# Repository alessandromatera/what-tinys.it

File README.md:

# "What Tinys.it?"
### A 3D printed LED watch with Atmega328P microcontroller programmed with Arduino

#### The Story
I wanted to build a LED watch with Arduino but, searching on the web, i could not find what i was looking for. So I've decided to build my own.
I wanted to use Attiny85 microcontroller from my board [Tinys](http://www.tinys.it/) but it has only few I/O and can't be used to drive many LEDs. So i decided to use an Atmega328P (the same micro of Arduino UNO board) in TQFP package with 32 pin.

For perfect timing i've used a 32.768 KHz Crystal connected to Xtal pins of Atmega328p running in asynchronous mode. In this way i can use internal 8Mhz oscillator as main clock of the microcontroller and the overflow of timer2 (used for the external crystal) as interrupt for increase the seconds.

Why 32.768Khz Crystal? Because using prescaler to 128 we have 256 Hz, so 1 overflow/sec. It's the most used crystal for watches for this reason.

What about the name? Well, my web site is [Tinys.it](http://www.tinys.it/) :D

#### The Project
I wanted to build a watch with 60 LEDs but to keep the clock size small, i've decide to use only 32 LED (1 LED/100 seconds). But even if the microcontroller has 32 pin, they aren't all I/O: only 25 pins can be used for the 32 LEDs and the button. To drive a larger number of LEDs with few pins i've used the [Charlieplexing Matrix](http://en.wikipedia.org/wiki/Charlieplexing), in this way i can drive 6 LEDs with only 3 Pins. Becouse i can't use two different color of LEDs, to distinguish between hours and minutes, the minutes LED is blinking. 

To reduce battery drain the watch is always in sleep. To show-up the time is needed to press the button.

As the clock hands, the hours LED isn't stay in the same position: is moving a bit, consequently to minutes.

The watch is powered by a 3 Volt CR2032 battery. With this battery the LEDs resistors can be shorted.

#### The Firmware
After setup the timer2 overflow interrupt and the button change-pin interrupt, the microcontroller goes to sleep. Every time the timer2 goes overflow (1 overflow/seconds) the microcontroller wakes up and increase the seconds. 

When the button is pressed for a small period of time, the button's interrupt occur and the time is show up. Instead, if the button is pressed for two seconds, we entering in programming mode, where we can set the time: after all LEDs are turned on, we can release the button and the current hours LED is turned on. Pressing one time the button hours change to the next. To record the current hours you need to press the button for about 2 seconds. After the hours LED is switched off, release the button and the minutes LED is turned on. Like the hours LED push the button to choose the right minutes and then long press to record the minutes. After the minutes LED is turned off, all LEDs is turned on. The corrected time is show up.

#### Upload the sketch
To Upload the firmware i use avr in Mac terminal and an Arduino UNO as ISP programmer. 

To do that follow these steps:

1. Connect the Arduino UNO board to PC or Mac.
2. Select the `ArduinoISP` sketch from `File -> Examples`
3. Upload the sketch to the Arduino UNO board
4. Open the watch sketch
5. Compile the sketch using Arduino IDE
6. Connect the SPI watch pins to Arduino UNO pins in this way:
	* Watch PIN `Reset - JP6` to Arduino PIN `10`
	* Watch PIN `11 - JP3` to Arduino PIN `11`
	* Watch PIN `12 - JP4` to Arduino PIN `12`
	* Watch PIN `13 - JP5` to Arduino PIN `13`
	* Watch PIN `V+ - JP1` to Arduino PIN `+3.3V`
	* Watch PIN `GND - JP2` to Arduino PIN `GND`
7. On Mac terminal (i think is similar for Windows/Linux users) write this
	```
	avrdude -v -v -v -v -cstk500v1 -pm328p  -P/dev/tty.usbmodemfa131 -b19200 -D -e -Ulock:w:0x3F:m -Uefuse:w:0x07:m -Uhfuse:w:0xDE:m -Ulfuse:w:0xE2:m -Uflash:w:/path/of/your/hex/file.hex:i
	```
	
	where:
	 - `tty.usbmodemfa131` is the serial port of Arduino board
	 - `/path/of/your/hex/file.hex` is the path of `.hex` file that can be taken from the Arduino IDE enabling `verbose output` from `Preferences -> Show Verbose output during: -> compilation`
	
All this stuff because i wanted to program the board using SPI not using Arduino bootloader. I Think that the watch can be programmed like an Arduino UNO using the `breadboard 8Mhz internal oscillator` bootloader and soldering two wires to pin `0` and `1` of the watch, but i've not tried it.

I've have used fuses for disabling `BOD` so you need to modify the bootloader of Arduino to do this. (Maybe you can do this in sketch?).

#### The Case
The 3D printed case was realized by my brother Andrea Matera.

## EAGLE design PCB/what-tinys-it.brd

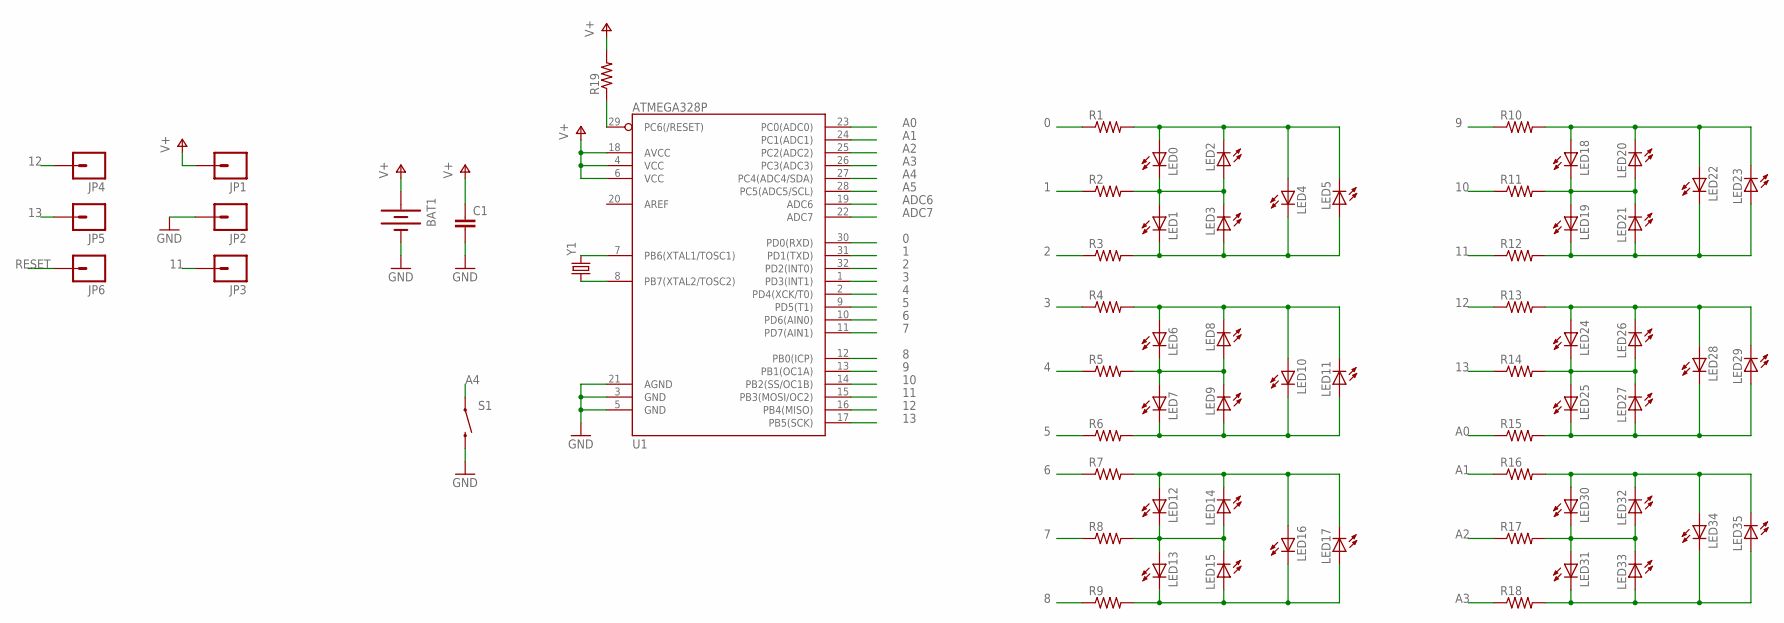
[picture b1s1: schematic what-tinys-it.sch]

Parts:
BAT1: BATTERY20SMD; BATTCON_20MM
C1: C-EUC0805; C0805
JP1, JP2, JP3, JP4, JP5, JP6: M01SMDNS; 1X01NS
LED0, LED1, LED2, LED3, LED4, LED5, LED6, LED7, LED8, LED9, LED10, LED11, LED12, LED13, LED14, LED15, LED16, LED17, LED18, LED19, LED20, LED21, LED22, LED23, LED24, LED25, LED26, LED27, LED28, LED29, LED30, LED31, LED32, LED33, LED34, LED35: LEDCHIPLED_0805; CHIPLED_0805
R1, R2, R3, R4, R5, R6, R7, R8, R9, R10, R11, R12, R13, R14, R15, R16, R17, R18, R19: RESISTOR0805-RES; 0805
S1: SWITCH-MOMENTARY-2SMD-3; TACTILE_SWITCH_SMD-3
U1: ATMEGA328P; TQFP32-08
Y1: CRYSTAL32-SMD; CRYSTAL-32KHZ-SMD

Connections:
0: R1.1, U1.30 (PD0(RXD))
1: R2.1, U1.31 (PD1(TXD))
2: R3.1, U1.32 (PD2(INT0))
3: R4.1, U1.1 (PD3(INT1))
4: R5.1, U1.2 (PD4(XCK/T0))
5: R6.1, U1.9 (PD5(T1))
6: R7.1, U1.10 (PD6(AIN0))
7: R8.1, U1.11 (PD7(AIN1))
8: R9.1, U1.12 (PB0(ICP))
9: R10.1, U1.13 (PB1(OC1A))
10: R11.1, U1.14 (PB2(SS/OC1B))
11: JP3.1, R12.1, U1.15 (PB3(MOSI/OC2))
12: JP4.1, R13.1, U1.16 (PB4(MISO))
13: JP5.1, R14.1, U1.17 (PB5(SCK))
A0: R15.1, U1.23 (PC0(ADC0))
A1: R16.1, U1.24 (PC1(ADC1))
A2: R17.1, U1.25 (PC2(ADC2))
A3: R18.1, U1.26 (PC3(ADC3))
A4: S1.1, U1.27 (PC4(ADC4/SDA))
A5: U1.28 (PC5(ADC5/SCL))
ADC6: U1.19 (ADC6)
ADC7: U1.22 (ADC7)
GND: BAT1.2 (-), C1.2, JP2.1, S1.4 (2), U1.3 (GND), U1.5 (GND), U1.21 (AGND)
unnamed: LED0.A, LED2.C, LED4.A, LED5.C, R1.2
unnamed: LED6.A, LED8.C, LED10.A, LED11.C, R4.2
unnamed: LED0.C, LED1.A, LED2.A, LED3.C, R2.2
unnamed: LED1.C, LED3.A, LED4.C, LED5.A, R3.2
unnamed: LED12.A, LED14.C, LED16.A, LED17.C, R7.2
unnamed: LED6.C, LED7.A, LED8.A, LED9.C, R5.2
unnamed: LED7.C, LED9.A, LED10.C, LED11.A, R6.2
unnamed: LED18.A, LED20.C, LED22.A, LED23.C, R10.2
unnamed: LED12.C, LED13.A, LED14.A, LED15.C, R8.2
unnamed: LED13.C, LED15.A, LED16.C, LED17.A, R9.2
unnamed: LED18.C, LED19.A, LED20.A, LED21.C, R11.2
unnamed: LED24.A, LED26.C, LED28.A, LED29.C, R13.2
unnamed: LED19.C, LED21.A, LED22.C, LED23.A, R12.2
unnamed: LED24.C, LED25.A, LED26.A, LED27.C, R14.2
unnamed: LED30.A, LED32.C, LED34.A, LED35.C, R16.2
unnamed: U1.7 (PB6(XTAL1/TOSC1)), Y1.X2 (2)
unnamed: LED25.C, LED27.A, LED28.C, LED29.A, R15.2
unnamed: U1.8 (PB7(XTAL2/TOSC2)), Y1.X1 (1)
unnamed: LED30.C, LED31.A, LED32.A, LED33.C, R17.2
unnamed: LED31.C, LED33.A, LED34.C, LED35.A, R18.2
RESET: JP6.1, R19.1, U1.29 (PC6(/RESET))
V+: BAT1.1 (+), C1.1, JP1.1, R19.2, U1.4 (VCC), U1.6 (VCC), U1.18 (AVCC)

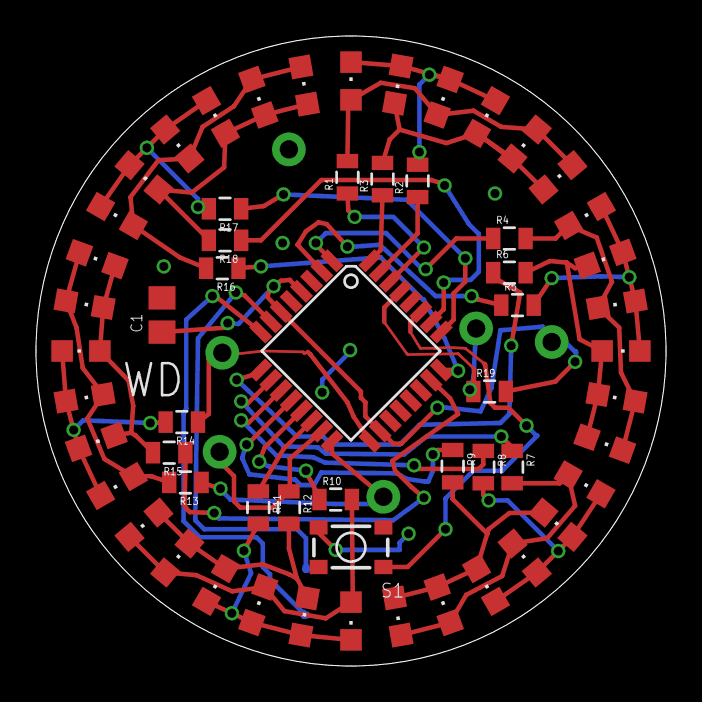
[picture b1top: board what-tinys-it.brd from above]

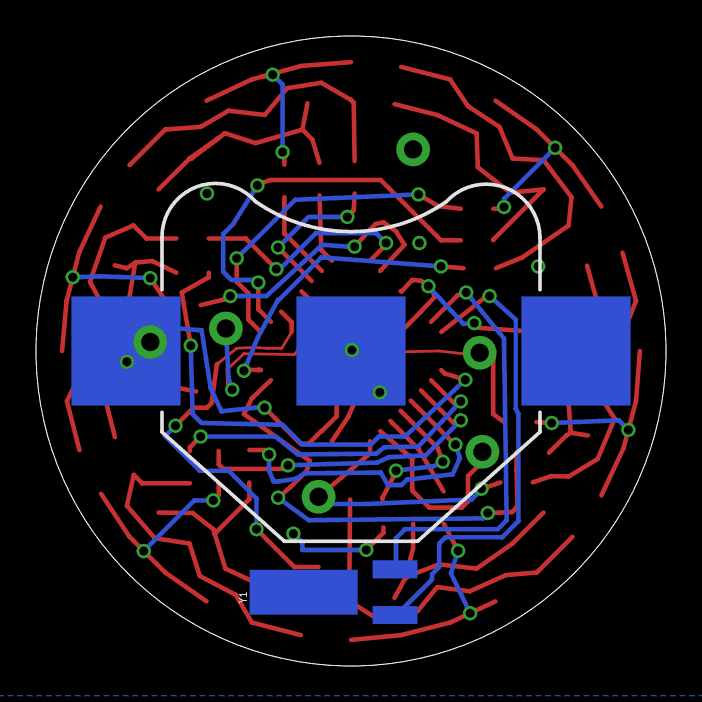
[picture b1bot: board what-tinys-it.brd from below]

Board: 2 copper layers, 35.0 x 35.0 mm, 66 parts (3 on the bottom side), 42 nets.

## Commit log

2015-04-01 Sketch
    Arduino Sketch file
2015-04-01 PCB and schematic
2015-04-01 3D printed Case
2015-04-01 how to upload firmware
2015-04-01 Sketch
2015-04-01 readme
2015-04-01 text

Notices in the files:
parts and their libraries:
SparkFun-DigitalIC: Licensing: CC v3.0 Share-Alike You are welcome to use this library for commercial purposes.
